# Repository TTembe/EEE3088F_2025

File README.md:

#  Micro-Mouse Power Subsystem – EEE3088F 2025

This repository contains the schematic, PCB layout, firmware, and documentation for the **Power Subsystem** of a maze-solving Micro-Mouse robot, developed as part of the EEE3088F course at the University of Cape Town.

---

##  Project Overview

This project focuses on the design, implementation, and testing of a compact and efficient **Power Subsystem** for a Micro-Mouse (MM) robot.

The power module is responsible for delivering regulated voltages, safe battery charging, motor power distribution, and real-time monitoring all within a space- and cost-constrained printed circuit board (PCB) footprint. It was developed to integrate seamlessly with the rest of the Micro-Mouse system, which includes processing, sensing, and control subsystems.

This subsystem ensures that all other modules in the robot receive stable power while providing built-in protection, control, and monitoring features. Its design includes features like dual-mode battery charging, USB-C PD negotiation, high-side switching for external loads, and I2C-based current/voltage sensing. 

The design adheres to the full set of requirements for the complete robot. The board is designed for manufacturability via JLCPCB and optimized for both performance and academic assessment.

---

##  Features

-  **Dual Motor Power Support**  
  Powers up to 4 brushed DC motors with reliable bidirectional control  including two high-current auxiliary motors (500mA each).

-  **Intelligent Battery Charging**  
  Automatically charges a single-cell LiPo battery from a 9V input using a selectable current mode: safe slow charge (~200mA) or faster charging (~600mA ±100mA).

-  **Real-Time Power Monitoring**  
  Monitors battery voltage and current in real-time using the INA219 sensor connected to the I²C bus, enabling diagnostics and data logging.

-  **USB-C Power Delivery Integration**  
  Negotiates 9V from compliant USB-C PD sources via the CH224K controller to support flexible charging and system power input.

-  **External Load Control**  
  Includes two high-side load switches for driving external 5V peripherals up to 1A each, with control via GPIO from the main processor.

-  **Precision Voltage Regulation**  
  Provides clean and accurate 3.3V (±5%) and 5V (±5%) rails for digital logic and sensor subsystems, supporting peak currents of up to 1.5A.

-  **Efficient Power Switching**  
  Features a physical ON/OFF switch that disables both 3.3V and 5V rails when inactive, reducing standby battery draw to under 30μA.

-  **Compact PCB Footprint**  
  Fully integrated on a compact 82mm × 60mm 2-layer PCB, designed for modular stacking with the micro-mouse system.

-  **Cost-Effective Design**  
  Uses carefully selected components and efficient routing to stay well within the \$70 total budget limit for the project.

---

## Repository Structure

```bash
├── hardware/
│   ├── PCB_KiCad/             # Schematic and PCB layout (KiCad)
│   ├── Gerber_Files/          # JLCPCB-ready fabrication files
│   └── BOM/                   # Bill of Materials (.xlsx and .tex)
│
├── firmware/
│   ├── PowerControl/          # Firmware for fast charge control via PB4
│   └── INA219_Test/           # Firmware to read INA219 values via I2C
│
├── test_procedures/
│   └── ATP_Documents/         # Detailed Acceptance Test Procedures
│
├── docs/
│   ├── Report_Final.pdf       # Final academic report
│   └── Images/                # System diagrams, PCB renders
│
└── README.md

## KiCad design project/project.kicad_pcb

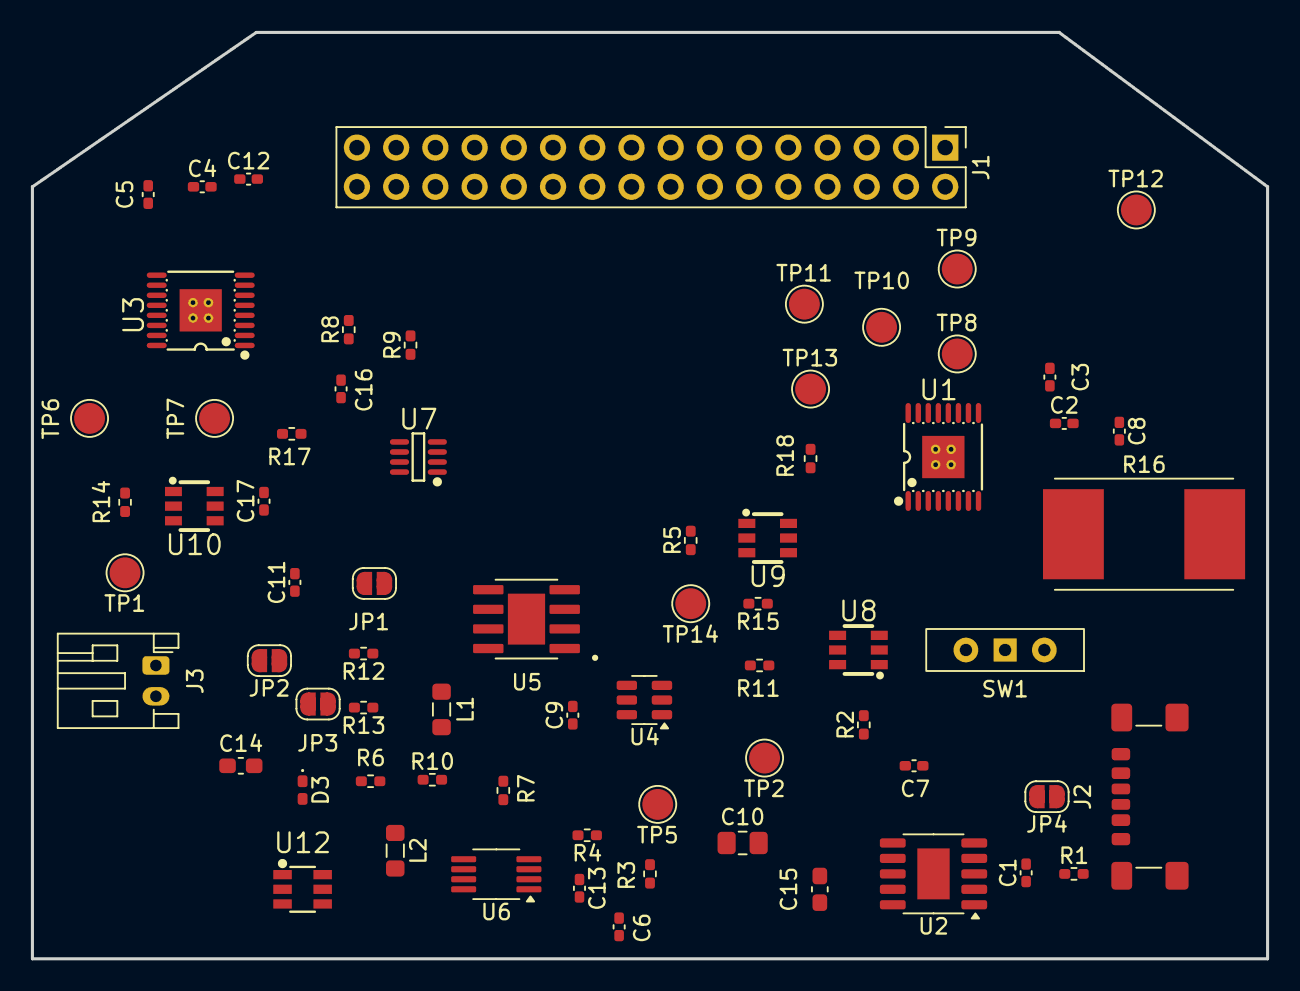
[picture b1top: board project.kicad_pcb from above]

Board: 2 copper layers, 80.0 x 60.0 mm, 69 parts (0 on the bottom side), 57 nets, no tracks yet.

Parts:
C1: 1u; C_0402_1005Metric_Pad0.74x0.62mm_HandSolder
C2, C4, C7: 10uF; C_0402_1005Metric_Pad0.74x0.62mm_HandSolder
C3, C5: 2.2uF; C_0402_1005Metric_Pad0.74x0.62mm_HandSolder
C6, C13: 4.7u; C_0402_1005Metric_Pad0.74x0.62mm_HandSolder
C8, C12: 10nF; C_0402_1005Metric_Pad0.74x0.62mm_HandSolder
C9: 100n; C_0402_1005Metric_Pad0.74x0.62mm_HandSolder
C10: 47u; C_0805_2012Metric_Pad1.18x1.45mm_HandSolder
C11: 10u; C_0402_1005Metric_Pad0.74x0.62mm_HandSolder
C14, C15: 22u; C_0603_1608Metric_Pad1.08x0.95mm_HandSolder
C16, C17: 1uF; C_0402_1005Metric_Pad0.74x0.62mm_HandSolder
D3: D_Small; D_0402_1005Metric_Pad0.77x0.64mm_HandSolder
J1: Conn_02x16_Odd_Even; PinHeader_2x16_P2.54mm_Vertical
J2: TYPE-C 6P(040新); USB_C_Receptacle_GCT_USB4135-GF-A_6P_TopMnt_Horizontal
J3: Conn_01x02_Pin; JST_PH_S2B-PH-K_1x02_P2.00mm_Horizontal
JP1, JP2, JP3, JP4: Jumper_2_Open; SolderJumper-2_P1.3mm_Open_RoundedPad1.0x1.5mm
L1: 4.7uH; L_0805_2012Metric_Pad1.05x1.20mm_HandSolder
L2: 4.7u; L_0805_2012Metric_Pad1.05x1.20mm_HandSolder
R1, R12, R13: 1K; R_0402_1005Metric_Pad0.72x0.64mm_HandSolder
R2, R3, R7: 10K; R_0402_1005Metric_Pad0.72x0.64mm_HandSolder
R4: 33K; R_0402_1005Metric_Pad0.72x0.64mm_HandSolder
R5, R14: 10k; R_0402_1005Metric_Pad0.72x0.64mm_HandSolder
R6: 100K; R_0402_1005Metric_Pad0.72x0.64mm_HandSolder
R8, R9: 4.7k; R_0402_1005Metric_Pad0.72x0.64mm_HandSolder
R10: 51K; R_0402_1005Metric_Pad0.72x0.64mm_HandSolder
R11: 5.6K; R_0402_1005Metric_Pad0.72x0.64mm_HandSolder
R15: 1.5K; R_0402_1005Metric_Pad0.72x0.64mm_HandSolder
R16: 0.5m; R_Shunt_Vishay_WSR2_WSR3
R17, R18: 200m; R_0402_1005Metric_Pad0.72x0.64mm_HandSolder
SW1: SS-12D10L9; SW_Slide-03_Wuerth-WS-SLTV_10x2.5x6.4_P2.54mm
TP1, TP2, TP5, TP6, TP7, TP8, TP9, TP10, TP11, TP12, TP13, TP14: TestPoint; TestPoint_Pad_D2.0mm
U1, U3: DRV8833PWPR; TSSOP-16_L5.0-W4.4-P0.65-LS6.4-BL-EP
U2: CH224K; SSOP-10-1EP_3.9x4.9mm_P1mm_EP2.1x3.3mm
U4: AP63203WU; TSOT-23-6
U5: TP4056
U6: AP2114; MSOP-8_3x3mm_P0.65mm
U7: INA219AIDCNR; SOT-23-8_L3.0-W1.7-P0.65-LS2.8-BR
U8: TS5A3159ADBVR; SOT-23-6_L2.9-W1.6-P0.95-LS2.8-BR
U9, U10: TPS22965DSGR; SOT-23-6_L2.9-W1.6-P0.95-LS2.8-BR
U12: MT3608L; SOT-23-6_L2.9-W1.6-P0.95-LS2.8-BL_3

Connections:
/3V3 Out: C13.1, J1.18, R4.1, R8.1, R9.1, U6.3 (OUT), U7.4 (VS), U7.8 (A1)
/5V Out: C14.1, C16.1, C17.1, D3.1 (K), J1.20, R6.1, U8.5 (V+), U9.1 (VIN), U9.2 (VIN), U9.4 (VBIAS), U10.1 (VIN), U10.2 (VIN), U10.4 (VBIAS)
/BATT: J3.1, JP1.1 (A), R16.1, SW1.3 (A), TP2.1, U5.5 (BAT)
/Battery: C1.1, C2.2, C4.2, C6.1, C8.1, C12.1, C15.1, J1.14, L2.1, R1.1, SW1.1 (B), U1.1 (NSLEEP), U1.12 (VM), U2.1 (VDD), U3.1 (NSLEEP), U3.12 (VM), U6.1 (EN), U6.2 (IN), U12.4 (EN), U12.5 (VIN)
/CTRL_EXT_LOAD1: J1.25, U10.3 (ON)
/CTRL_EXT_LOAD2: J1.7, U9.3 (ON)
/EXT_LOAD1_OUT: J1.21, R14.1, TP1.1
/EXT_LOAD2_OUT: J1.11, R5.1, TP14.1
/FAST_CHARGE_CTRL: J1.13, U8.6 (IN)
/HV: C7.1, J1.22, U4.2 (EN), U4.3 (IN)
/I2C1_SCL: J1.16, R8.2, U7.5 (SCL)
/I2C1_SDA: J1.17, R9.2, U7.6 (SDA)
/MOTOR1_A_OUT: J1.32, TP10.1, U1.2 (AOUT1)
/MOTOR1_B_OUT: J1.31, TP11.1, U1.4 (AOUT2)
/MOTOR1_CTRL1: J1.28, U1.16 (AIN1)
/MOTOR1_CTRL2: J1.30, U1.15 (AIN2)
/MOTOR2_A_OUT: J1.2, TP12.1, U1.7 (BOUT1)
/MOTOR2_B_OUT: J1.1, TP13.1, U1.5 (BOUT2)
/MOTOR2_CTRL1: J1.4, U1.9 (BIN1)
/MOTOR2_CTRL2: J1.6, U1.10 (BIN2)
/MOTOR3_A_OUT: J1.27, TP6.1, U3.2 (AOUT1)
/MOTOR3_B_OUT: J1.29, TP7.1, U3.4 (AOUT2)
/MOTOR3_CTRL1: J1.24, U3.16 (AIN1)
/MOTOR3_CTRL2: J1.26, U3.15 (AIN2)
/MOTOR4_A_OUT: J1.3, TP8.1, U3.7 (BOUT1)
/MOTOR4_B_OUT: J1.5, TP9.1, U3.5 (BOUT2)
/MOTOR4_CTRL1: J1.8, U3.9 (BIN1)
/MOTOR4_CTRL2: J1.10, U3.10 (BIN2)
GND: C1.2, C2.1, C3.1, C4.1, C5.1, C6.2, C7.2, C10.2, C11.2, C13.2, C14.2, C15.2, C16.2, C17.2, J1.19, J1.23, J2.A12 (GND), J2.B12 (GND), J2.S1 (SHIELD), J3.2, R3.2, R5.2, R7.2, R10.2, R11.2, R14.2, R15.1, R17.2, R18.2, U1.13 (GND), U1.17 (EXP), U2.2 (CFG2), U2.3 (CFG3), U2.9 (CFG1), U2.11 (GND), U3.13 (GND), U3.17 (EXP), U4.4 (GND), U5.1 (TEMP), U5.3 (GND), U6.5 (GND), U6.6 (GND), U6.7 (GND), U6.8 (GND), U7.3 (GND), U7.7 (A0), U8.2 (GND), U9.5 (GND), U10.5 (GND), U12.2 (GND)
unnamed: D3.2 (A), L2.2, U12.1 (SW)
unnamed: J2.A5 (CC1), U2.7 (CC1)
unnamed: J2.B5 (CC2), U2.6 (CC2)
unnamed: J2.A9 (VBUS), J2.B9 (VBUS), R1.2, R2.2
unnamed: C11.1, JP1.2 (B)
unnamed: JP2.1 (A), R12.1
unnamed: C10.1, JP2.2 (B), JP3.1 (A), L1.2, TP5.1, U4.1 (FB), U5.4 (VCC), U5.8 (CE)
unnamed: JP3.2 (B), R13.1
unnamed: JP4.1 (A), U2.4 (DP)
unnamed: JP4.2 (B), U2.5 (DM)
unnamed: R18.1, U1.3 (AISEN), U1.6 (BISEN)
unnamed: C8.2, U1.11 (VCP)
unnamed: C3.2, U1.14 (VINT)
unnamed: R2.1, U2.8 (VBUS)
unnamed: R17.1, U3.3 (AISEN), U3.6 (BISEN)
unnamed: C12.2, U3.11 (VCP)
unnamed: C5.2, U3.14 (VINT)
unnamed: C9.1, U4.6 (BST)
unnamed: C9.2, L1.1, U4.5 (SW)
unnamed: U5.2 (PROG), U8.4 (COM)
unnamed: R13.2, U5.7 (~CHRG)
unnamed: R12.2, U5.6 (~STDBY)
unnamed: R3.1, R4.2, U6.4 (ADJ)
unnamed: R16.2, U7.1 (IN+)
unnamed: R15.2, U8.3 (NC)
unnamed: R11.1, U8.1 (NO)
unnamed: R6.2, R7.1, U12.3 (FB)
unnamed: R10.1, U12.6 (OC)

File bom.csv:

Designator,Footprint,Quantity,Value,LCSC Part #
C1,0402,1,1u,C52923
C10,0805,1,47u,C16780
C11,0402,1,10u,C15525
"C12, C8",0402,2,10nF,C15525
"C13, C6",0402,2,4.7u, C23733
"C14, C15",0603,2,22u,C59461
"C16, C17, C18, C19",0402,4,1uF,C52923
"C2, C4, C7",0402,3,10uF,C15525
"C3, C5",0402,2,2.2uF,C12530
C9,0402,1,100n,C1525
D3,0402,1,D_Small,C2286
J1,PinHeader_2x16_P2.54mm_Vertical,1,Conn_02x16_Odd_Even,
J2,USB_C_Receptacle_GCT_USB4135-GF-A_6P_TopMnt_Horizontal,1,TYPE-C 6P(040新),C2887422
J3,JST_PH_S2B-PH-K_1x02_P2.00mm_Horizontal,1,Conn_01x02_Pin,
"JP1, JP2, JP3, JP4",SolderJumper-2_P1.3mm_Open_RoundedPad1.0x1.5mm,4,Jumper_2_Open,
L1,0805,1,4.7uH,C74314
L2,0805,1,4.7u,C74314
R1,0402,1,1K, C11702
R10,0402,1,51K, C25794
R11,0402,1,5.6K,
"R12, R13",0402,2,1K,C11702
"R14, R5",0402,2,10,C25077
R15,0402,1,1.5K,C25867
R16,R2512,1,3m,C5375459
"R17, R18",0402,2,200m,C270629
R2,0402,1,10K, C25744
"R3, R7",0402,2,10K,C25744
R4,0402,1,33K,C25779
R6,0402,1,100K,C25741
"R8, R9",0402,2,4.7k,C25900
SW1,SW_Slide-03_Wuerth-WS-SLTV_10x2.5x6.4_P2.54mm,1,SS-12D10L9,C319011
"TP1, TP10, TP11, TP12, TP13, TP14, TP2, TP3, TP5, TP6, TP7, TP8, TP9",TestPoint_Pad_D2.0mm,13,TestPoint,
"U1, U3",TSSOP-16_L5.0-W4.4-P0.65-LS6.4-BL-EP,2,DRV8833PWPR,C50506
"U10, U9",TPS22965DSGR,2,TPS22965DSGR,C122837
U11,SOT-23-8_L3.0-W1.7-P0.65-LS2.8-BR,1,INA219AIDCNR,C87469
U12,SOT-23-6_L2.9-W1.6-P0.95-LS2.8-BL_3,1,MT3608L,C2932326
U2,SSOP-10-1EP_3.9x4.9mm_P1mm_EP2.1x3.3mm,1,CH224K,C970725
U4,TSOT-23-6,1,AP63203WU,C780769
U5,TP4056,1,TP4056,C16581
U6,MSOP-8_3x3mm_P0.65mm,1,AP2114,C150716
U8,SOT-23-6_L2.9-W1.6-P0.95-LS2.8-BR,1,TS5A3159ADBVR,C128405

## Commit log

2025-03-26 USB and PD circuit
2025-03-26 Add switching circuits
2025-03-26 Add files via upload
    Update
2025-03-26 changed pull up resistor values
2025-03-27 change resistor
2025-03-27 add Oxolo subsections
2025-03-27 Rearranged.
2025-03-27 changed batt
2025-03-27 another update
2025-03-27 Step down voltage regulator
2025-03-27 Step up voltage regulation
2025-03-27 Assigning LCSC
2025-03-27 Open project
2025-03-27 assign footprint
2025-03-27 nothing
2025-03-27 Corrected LCSC
2025-03-27 CHANGED RESISTOR VALUE
2025-03-28 Footprints updated
2025-03-28 footprint assignment
2025-03-28 routing
2025-03-28 Rerouting
2025-03-28 layers
2025-04-08 checks
2025-04-08 Updates
    Changes datasheet names,updates PCB,fixex errors
2025-04-08 fixing errors on PCB
2025-04-08 assigning correct footprints
2025-04-09 import/export
